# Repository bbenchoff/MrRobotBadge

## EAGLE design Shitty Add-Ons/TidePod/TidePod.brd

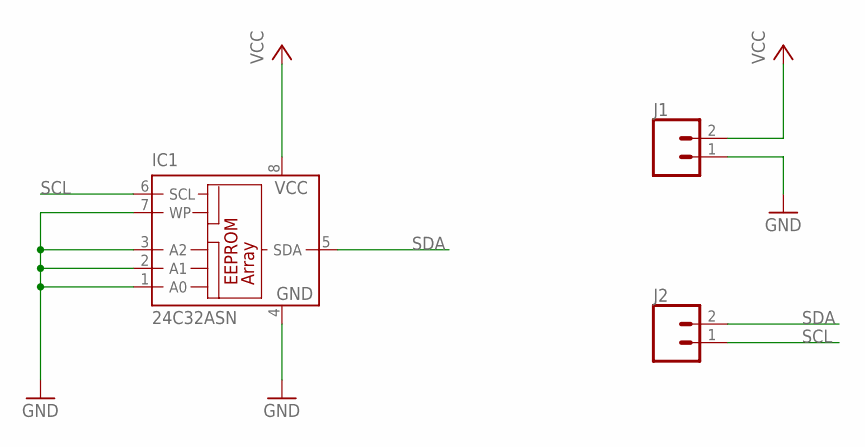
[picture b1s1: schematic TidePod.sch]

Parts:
IC1: 24C32ASN; SO-08
J1, J2: CONN_021X02_NO_SILK; 1X02_NO_SILK

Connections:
GND: IC1.1 (A0), IC1.2 (A1), IC1.3 (A2), IC1.4 (GND), IC1.7 (WP), J1.1
SCL: IC1.6 (SCL), J2.1
SDA: IC1.5 (SDA), J2.2
VCC: IC1.8 (VCC), J1.2

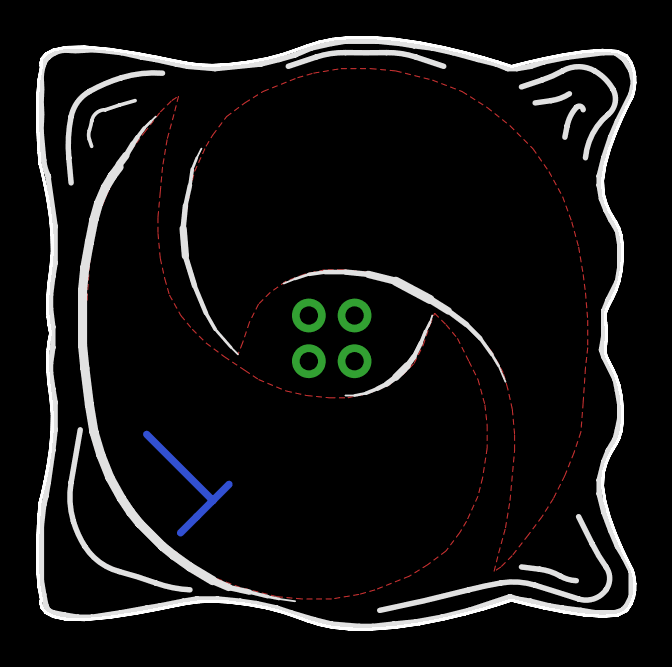
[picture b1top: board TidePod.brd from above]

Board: 2 copper layers, 33.2 x 32.9 mm, 3 parts (1 on the bottom side), 4 nets.

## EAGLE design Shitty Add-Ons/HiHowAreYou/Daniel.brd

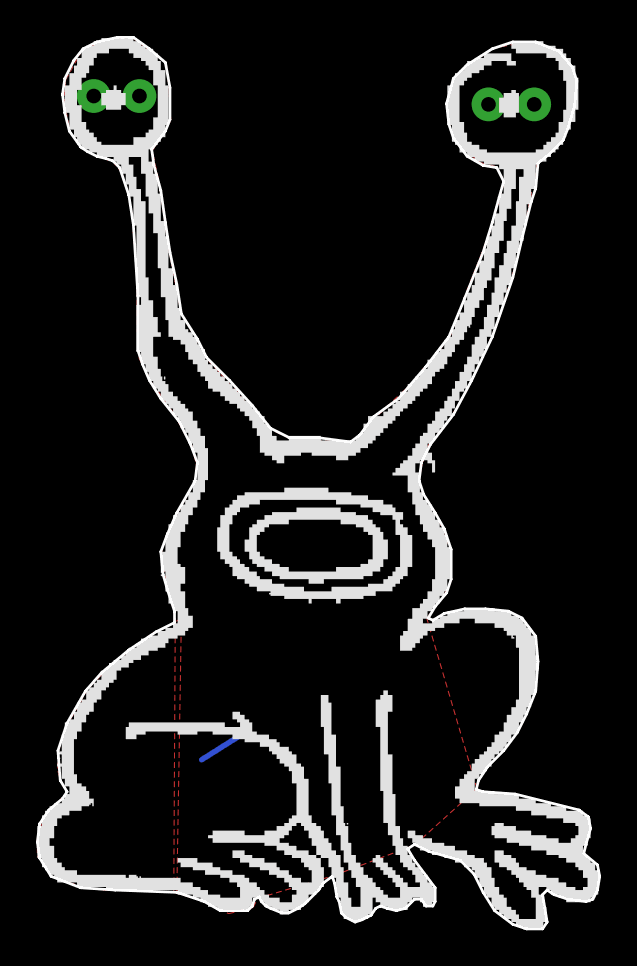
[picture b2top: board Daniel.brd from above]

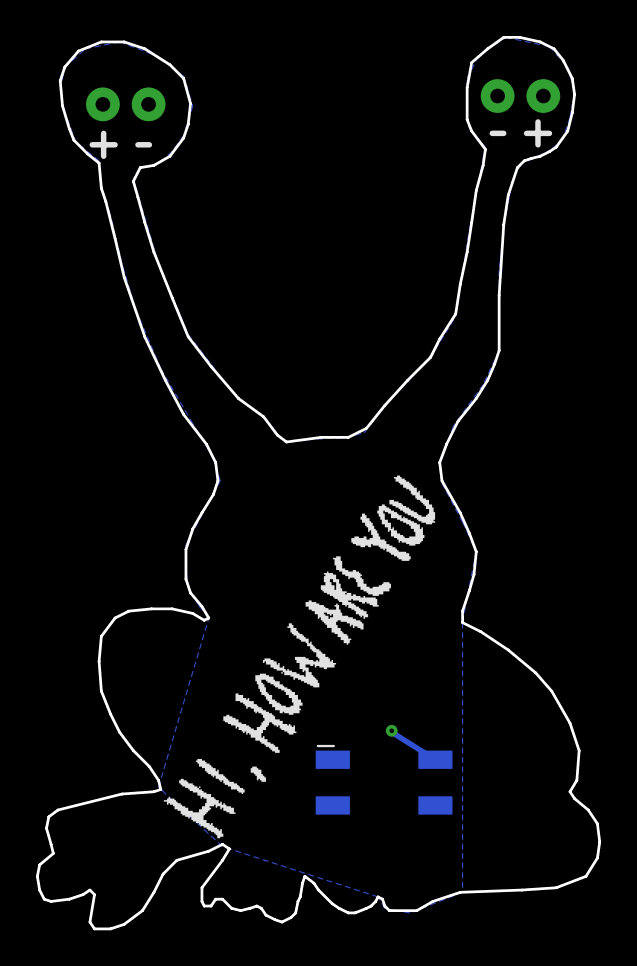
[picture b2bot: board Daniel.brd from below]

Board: 2 copper layers, 31.2 x 49.5 mm, 3 parts (2 on the bottom side), 2 nets.

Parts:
D3, D4: LED_5MM_NOSILK
U$1: CONN_2X2; 2X2_SMD

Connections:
GND: D3.K, D4.K, U$1.4
VCC: D3.A, D4.A, U$1.2

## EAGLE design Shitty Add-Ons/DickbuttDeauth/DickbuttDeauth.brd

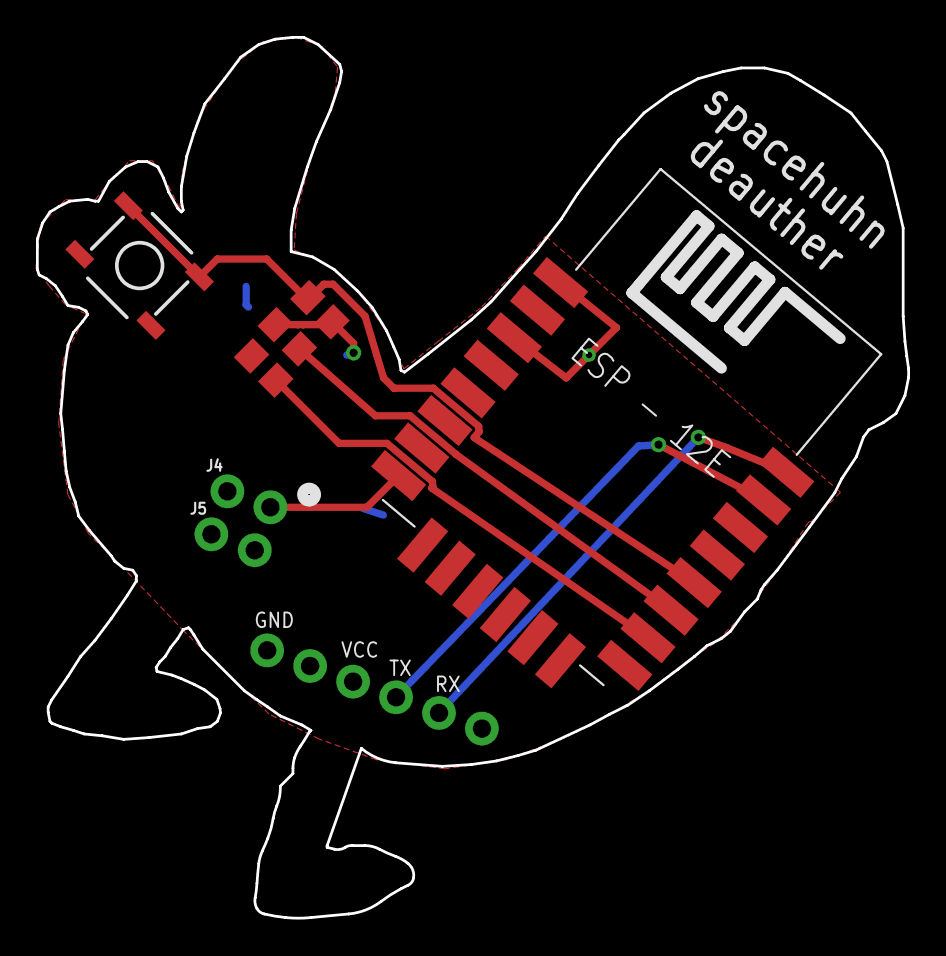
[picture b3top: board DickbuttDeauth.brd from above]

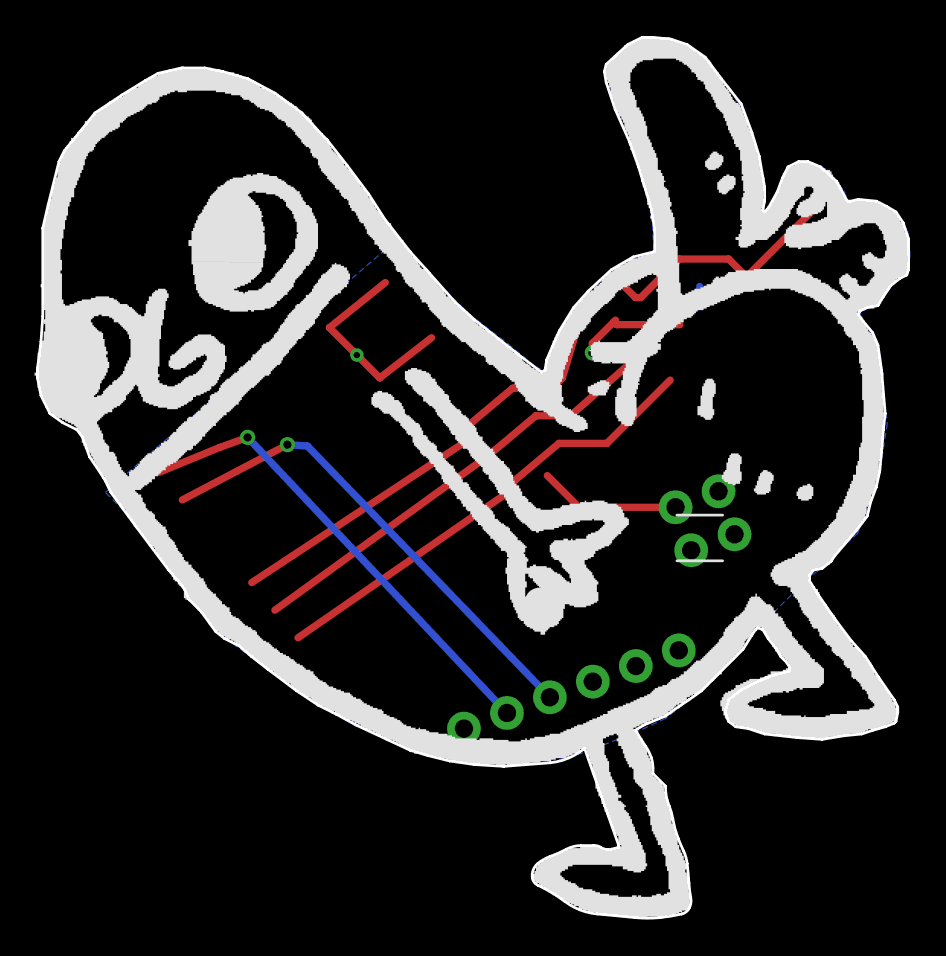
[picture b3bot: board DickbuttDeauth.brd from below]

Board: 2 copper layers, 48.4 x 48.9 mm, 10 parts (3 on the bottom side), 7 nets.

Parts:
J1: 1X06_NO_SILK
J2, J3, J4, J5: 1X01NS_KIT
R1, R2, R3: 10k; R0805
S1: TACTILE_SWITCH_SMD_5.2MM
U1: ESP12E-SMD

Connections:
GND: J1.6, J3.1, R2.1, S1.1, S1.2, U1.GND
unnamed: R3.2, U1.GPIO2
unnamed: R2.2, U1.GPIO15
unnamed: R1.1, S1.3, S1.4, U1.GPIO0
RX: J1.2, U1.TXD0
TX: J1.3, U1.RXD0
VCC: J1.4, J2.1, R1.2, R3.1, U1.CH_PD, U1.RESET, U1.VCC

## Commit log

2017-02-05 :confetti_ball: Added .gitattributes & .gitignore files
2018-08-17 Initial Dump
    Create repo
2018-08-20 Added gerbers
2019-09-14 adding bom
2020-07-24 Add firmware

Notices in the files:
parts and their libraries:
SparkFun-Connectors: Licensing: Creative Commons ShareAlike 4.0 International - https://creativecommons.org/licenses/by-sa/4.0
